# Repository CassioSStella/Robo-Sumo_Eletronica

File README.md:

markdown# 🤖 PatoBots — Eletrônica do Robô de Sumô

Repositório da seção de eletrônica para o desenvolvimento de um robô de sumô híbrido de 500g,
desenvolvido como atividade de trainee da equipe **PatoBots**.

---

## 📋 Sobre o Projeto

O projeto consiste no desenvolvimento do hardware eletrônico do robô, incluindo esquemáticos
e layout de PCB produzidos no **KiCad**. A especificação completa do projeto está disponível
na documentação da equipe no Notion:

🔗 [Projeto de Integração Trainees PatoBots — Sumô Híbrido 500g](https://www.notion.so/Projeto-de-Integra-o-Trainees-PatoBots-Desenvolvimento-de-Sum-H-brido-500g-327fba90dc5980c68d72c41331cd149f)

## 🚀 Como Começar

### Configuração do KiCad
Caso não tenha experiência com o KiCad, recomenda-se seguir a playlist introdutória:

🎬 [Playlist — Introdução ao KiCad](https://www.youtube.com/watch?v=tVLF8Y9jc6o&list=PL8kCnofYYWZrkhUis1svLGux1tjYNJy2Z)

### Importando componentes do SnapEDA
Para adicionar os modelos de símbolos e footprints baixados do SnapEDA ao KiCad:

🎬 [Como configurar arquivos do SnapEDA no KiCad](https://www.youtube.com/watch?v=W9cLnIjvybo)

---

## 📌 Referências

| Recurso | Descrição |
|---|---|
| [Dory — Project Neon](https://github.com/project-neon/Dory) | Robô de sumô com eletrônica feita em KiCad, usado como referência comparativa. Os modelos KiCad do Kit ESP32 Doit foram obtidos deste repositório. |

---

## 🛠️ Ferramentas Utilizadas

- [KiCad](https://www.kicad.org/) — EDA para esquemáticos e PCB
- [SnapEDA](https://www.snapeda.com/) — Biblioteca de componentes

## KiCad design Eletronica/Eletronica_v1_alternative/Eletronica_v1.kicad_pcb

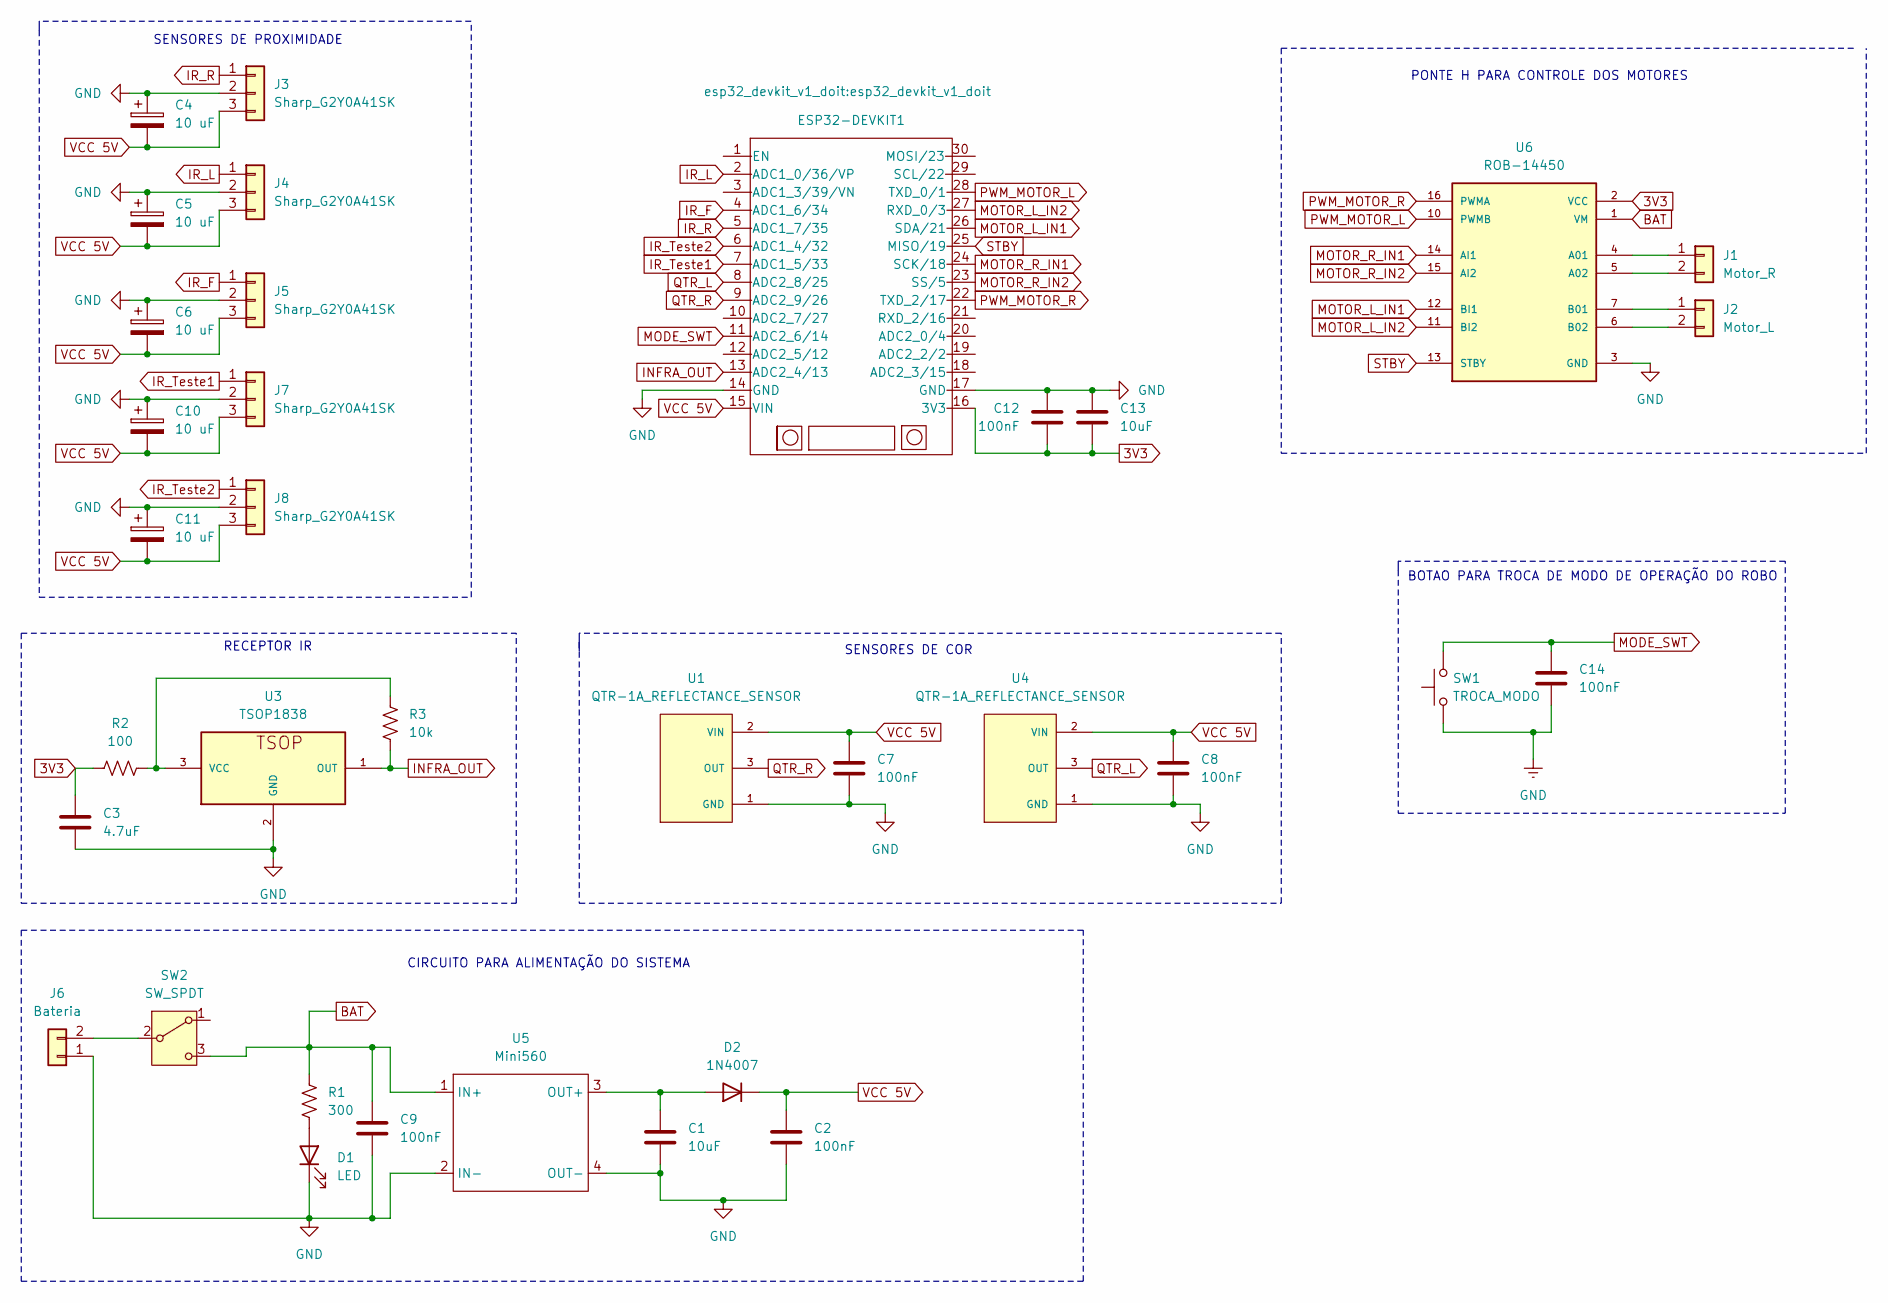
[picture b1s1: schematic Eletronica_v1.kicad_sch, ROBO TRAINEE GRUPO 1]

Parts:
C1, C13: 10uF; CP_Radial_D5.0mm_P2.50mm
C2, C7, C8, C9, C12, C14: 100nF; C_Disc_D5.0mm_W2.5mm_P5.00mm
C3: 4.7uF; CP_Radial_D5.0mm_P2.50mm
C4, C5, C6, C10, C11: 10 uF; CP_Radial_D5.0mm_P2.50mm
D1: LED; LED_D5.0mm
D2: 1N4007; D_DO-41_SOD81_P10.16mm_Horizontal
ESP32-DEVKIT1: esp32_devkit_v1_doit
J1: Motor_R; Molex_KK-254_AE-6410-02A_1x02_P2.54mm_Vertical
J2: Motor_L; Molex_KK-254_AE-6410-02A_1x02_P2.54mm_Vertical
J3, J4, J5, J7, J8: Sharp_G2Y0A41SK; JST_PH_B3B-PH-K_1x03_P2.00mm_Vertical
J6: Bateria; JST_EH_B2B-EH-A_1x02_P2.50mm_Vertical
R1: 300; R_Axial_DIN0207_L6.3mm_D2.5mm_P10.16mm_Horizontal
R2: 100; R_Axial_DIN0207_L6.3mm_D2.5mm_P10.16mm_Horizontal
R3: 10k; R_Axial_DIN0207_L6.3mm_D2.5mm_P10.16mm_Horizontal
SW1: TROCA_MODO; SW_Tactile_Straight_KSA0Axx1LFTR
SW2: SW_SPDT; SW_Slide-03_Wuerth-WS-SLTV_10x2.5x6.4_P2.54mm
U1, U4: QTR-1A_REFLECTANCE_SENSOR; SENSOR_QTR-1A_REFLECTANCE_SENSOR
U3: TSOP1838
U5: Mini560; Sem título
U6: ROB-14450; MODULE_ROB-14450; PARTREV 11-13-17

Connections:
3V3: C3.1, C12.2, C13.2, ESP32-DEVKIT1.16 (3V3), R2.1, U6.2 (VCC)
BAT: C9.1, R1.1, SW2.3 (C), U5.1 (IN+), U6.1 (VM)
GND: C1.2, C2.2, C3.2, C4.1, C5.1, C6.1, C7.2, C8.2, C9.2, C10.1, C11.1, C12.1, C13.1, C14.2, D1.1 (K), ESP32-DEVKIT1.14 (GND), ESP32-DEVKIT1.17 (GND), J3.2, J4.2, J5.2, J6.1, J7.2, J8.2, SW1.1, U1.1 (GND), U3.2 (GND), U4.1 (GND), U5.2 (IN-), U5.4 (OUT-), U6.3 (GND), U6.8 (GND), U6.9 (GND)
INFRA_OUT: ESP32-DEVKIT1.13 (ADC2_4/13), R3.2, U3.1 (OUT)
IR_F: ESP32-DEVKIT1.4 (ADC1_6/34), J5.1
IR_L: ESP32-DEVKIT1.2 (ADC1_0/36/VP), J4.1
IR_R: ESP32-DEVKIT1.5 (ADC1_7/35), J3.1
IR_Teste1: ESP32-DEVKIT1.7 (ADC1_5/33), J7.1
IR_Teste2: ESP32-DEVKIT1.6 (ADC1_4/32), J8.1
MODE_SWT: C14.1, ESP32-DEVKIT1.11 (ADC2_6/14), SW1.2
MOTOR_L_IN1: ESP32-DEVKIT1.26 (SDA/21), U6.12 (BI1)
MOTOR_L_IN2: ESP32-DEVKIT1.27 (RXD_0/3), U6.11 (BI2)
MOTOR_R_IN1: ESP32-DEVKIT1.24 (SCK/18), U6.14 (AI1)
MOTOR_R_IN2: ESP32-DEVKIT1.23 (SS/5), U6.15 (AI2)
unnamed: D1.2 (A), R1.2
unnamed: C1.1, D2.2 (A), U5.3 (OUT+)
unnamed: J1.1, U6.4 (A01)
unnamed: J1.2, U6.5 (A02)
unnamed: J2.1, U6.7 (B01)
unnamed: J2.2, U6.6 (B02)
unnamed: J6.2, SW2.2 (B)
unnamed: R2.2, R3.1, U3.3 (VCC)
PWM_MOTOR_L: ESP32-DEVKIT1.28 (TXD_0/1), U6.10 (PWMB)
PWM_MOTOR_R: ESP32-DEVKIT1.22 (TXD_2/17), U6.16 (PWMA)
QTR_L: ESP32-DEVKIT1.8 (ADC2_8/25), U4.3 (OUT)
QTR_R: ESP32-DEVKIT1.9 (ADC2_9/26), U1.3 (OUT)
STBY: ESP32-DEVKIT1.25 (MISO/19), U6.13 (STBY)
VCC 5V: C2.1, C4.2, C5.2, C6.2, C7.1, C8.1, C10.2, C11.2, D2.1 (K), ESP32-DEVKIT1.15 (VIN), J3.3, J4.3, J5.3, J7.3, J8.3, U1.2 (VIN), U4.2 (VIN)

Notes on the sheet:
PONTE H PARA CONTROLE DOS MOTORES
BOTAO PARA TROCA DE MODO DE OPERAÇÃO DO ROBO
SENSORES DE COR
SENSORES DE PROXIMIDADE
CIRCUITO PARA ALIMENTAÇÃO DO SISTEMA
RECEPTOR IR

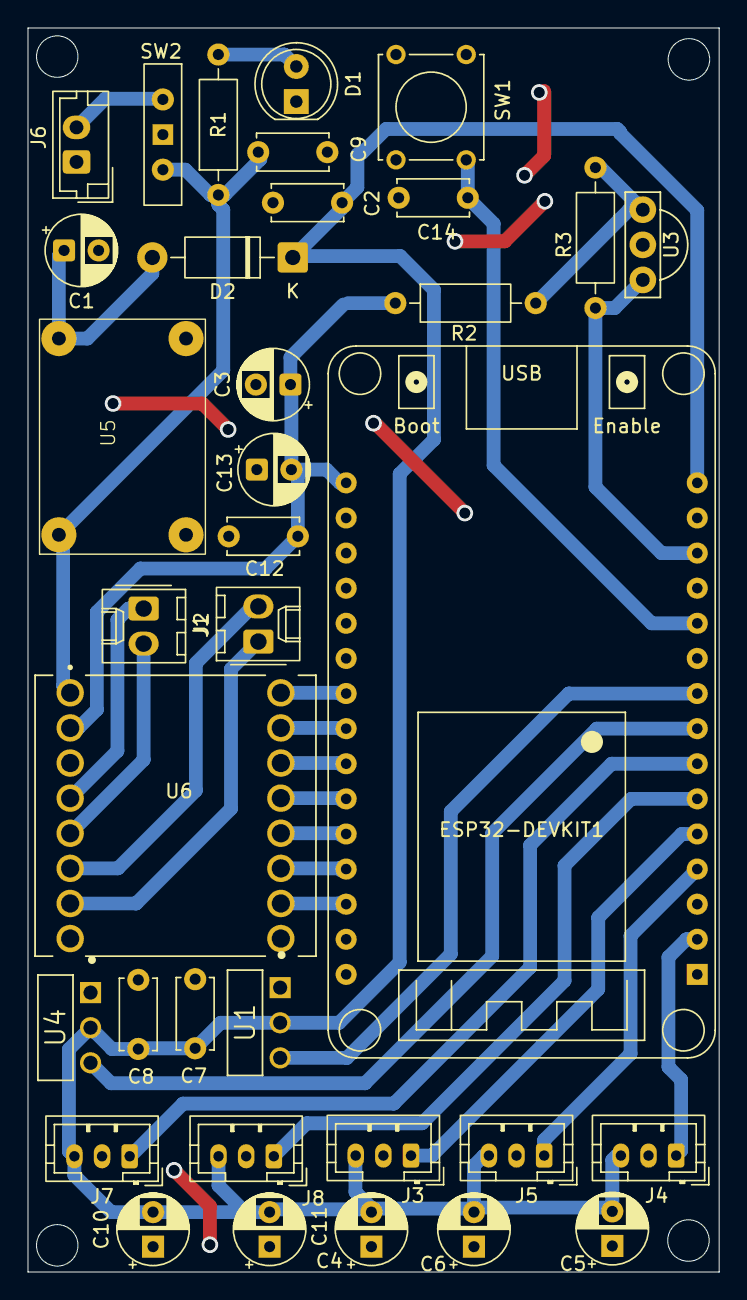
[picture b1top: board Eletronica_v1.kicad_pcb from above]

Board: 2 copper layers, 50.0 x 90.0 mm, 35 parts (0 on the bottom side), 28 nets.

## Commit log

2026-04-10 Estrutura inicial da etapa de eletroncia
2026-04-24 Corrigido circuito de alimentação e conexão dos periféricos
2026-05-20 Atualizado swtich e footprints
2026-05-29 Reduzido Capacitores, e tracado layout parcial da pcb
2026-06-18 Finalizado a versao funcional da placa
2026-06-18 Nova placa alternativa com 2 sensores sharp adicionais
